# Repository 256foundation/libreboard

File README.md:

# Libre-Board
Open Source Bitcoin Mining Control Board.
Learn more at https://libreboard.org/

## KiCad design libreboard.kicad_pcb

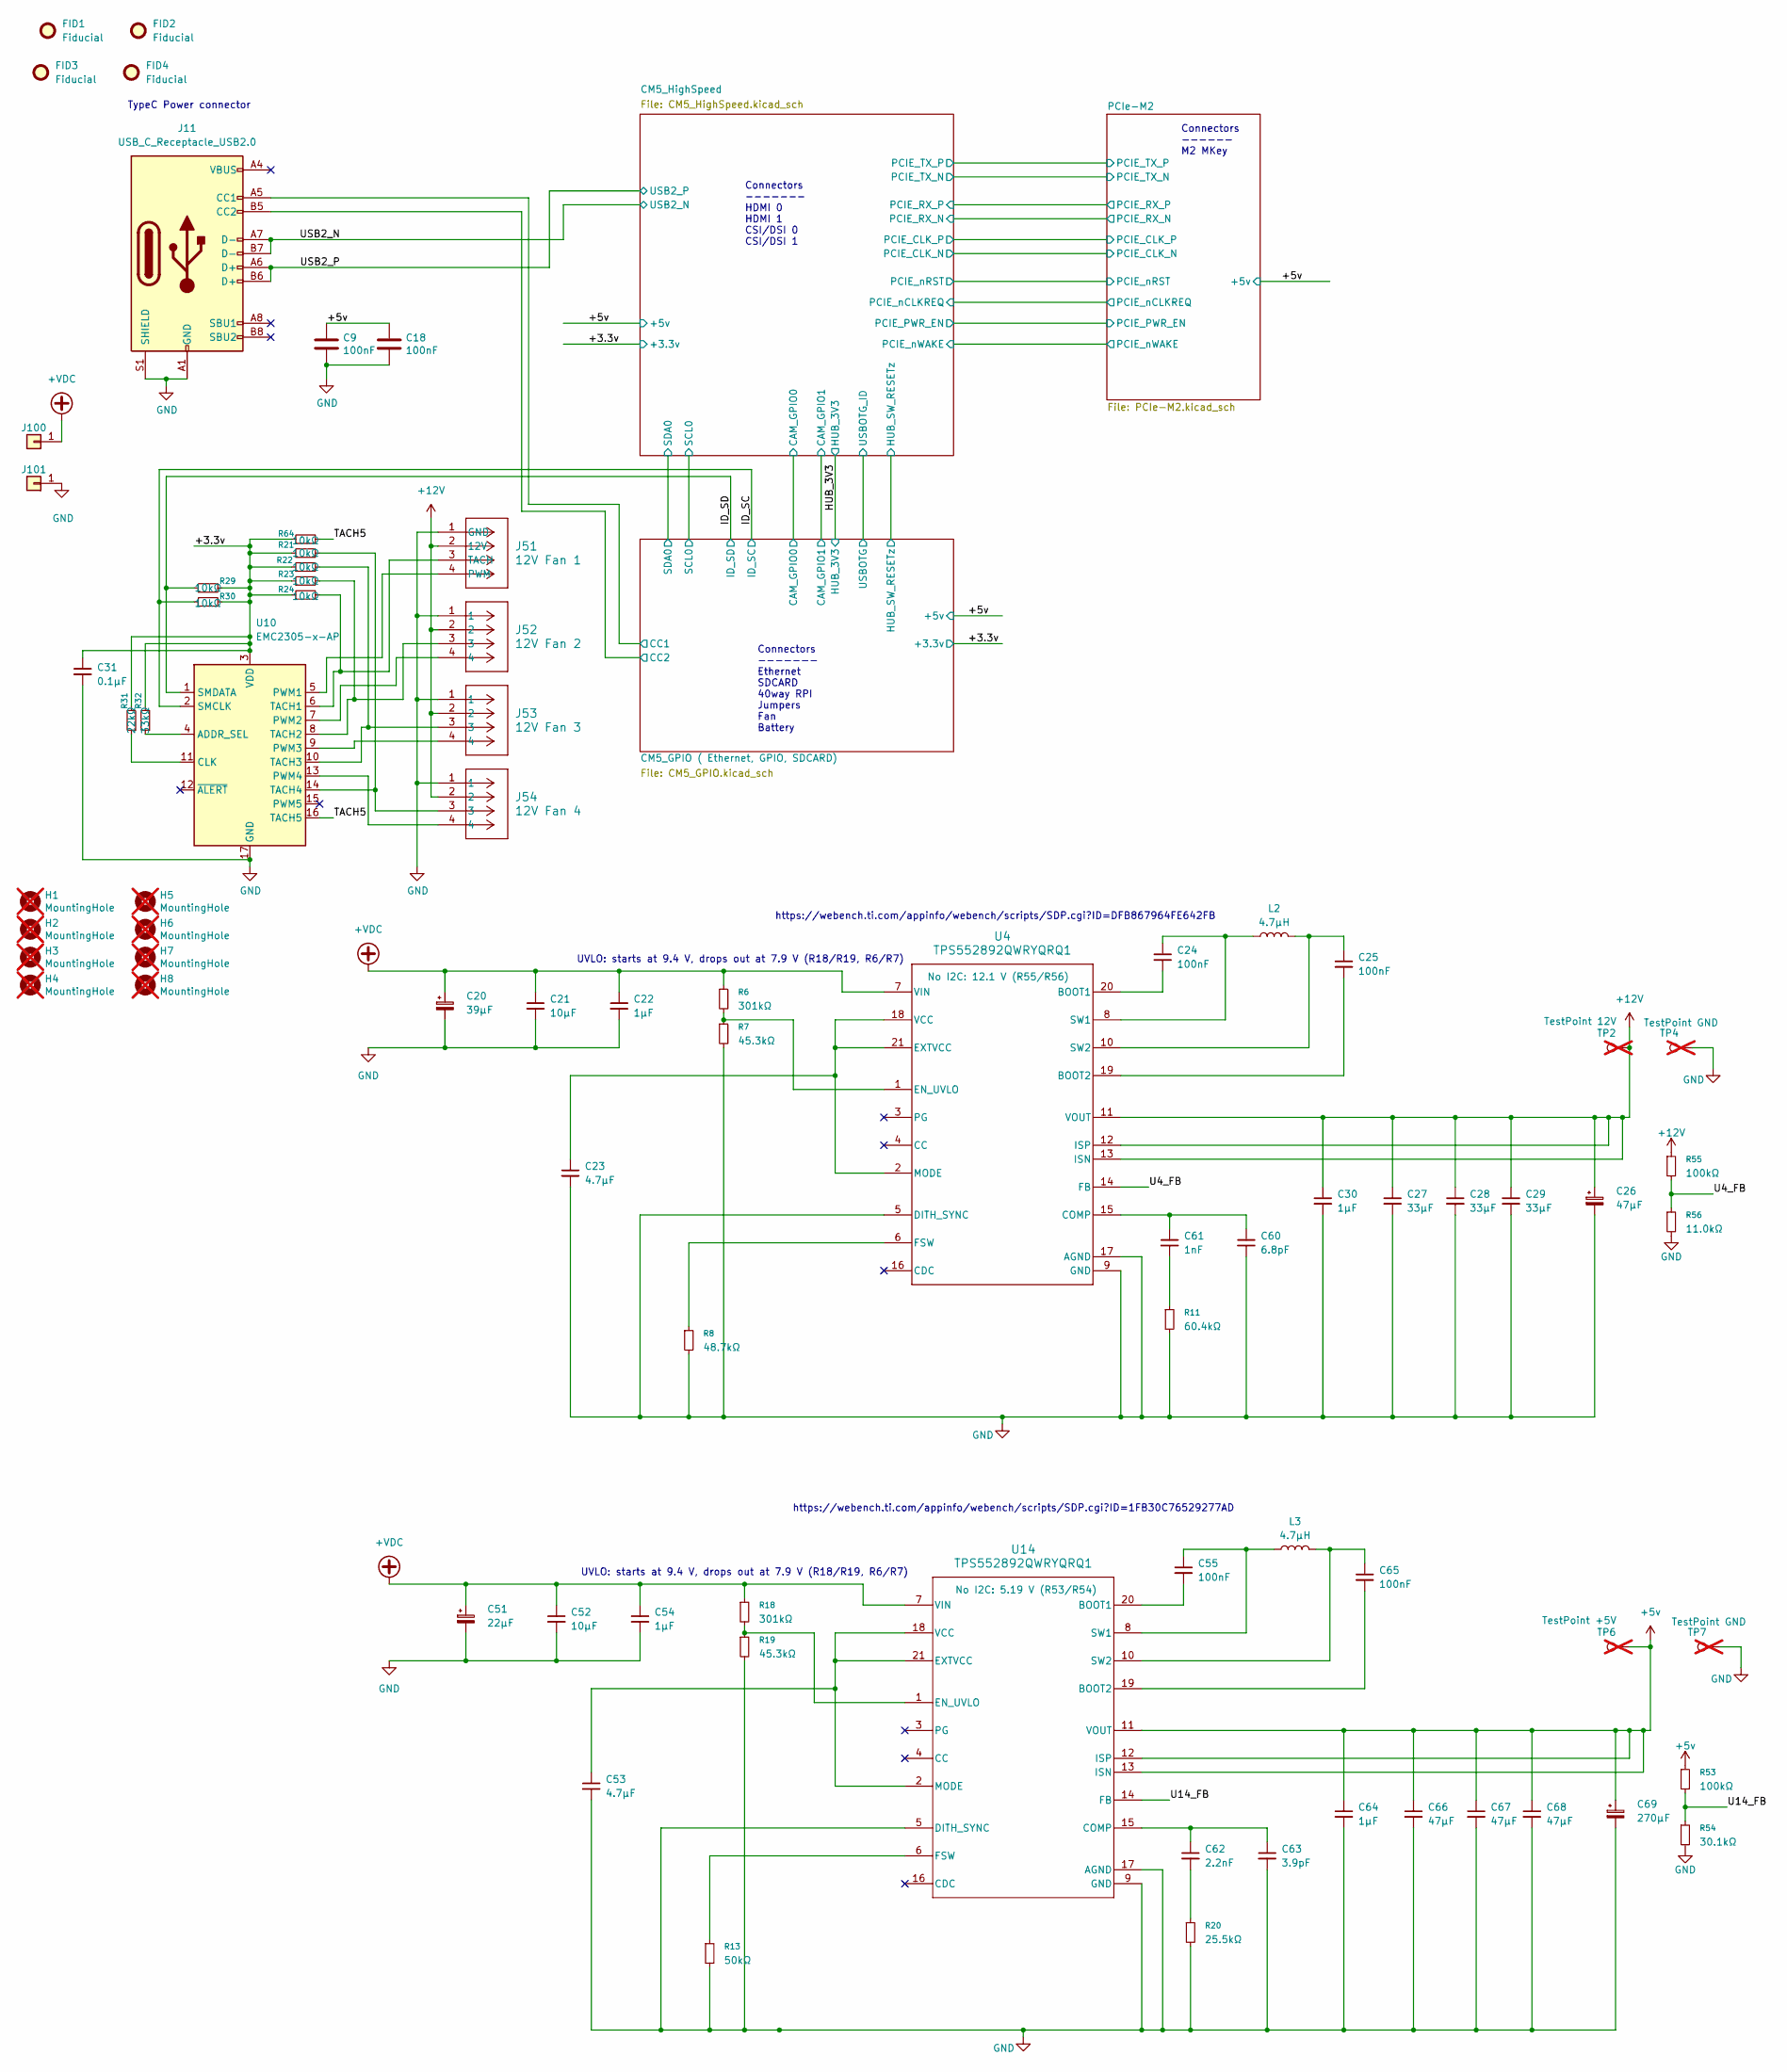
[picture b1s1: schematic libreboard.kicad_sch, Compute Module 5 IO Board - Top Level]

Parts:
C9, C18: 100nF; C_0402_1005Metric; Part Description Capacitor, Ceramic, 0.1µF, ±10%, 6.3V, 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; LCSC C1525
C20: 39µF; CP_Elec_8x6.7; Part Description Capacitor, Aluminum, 39µF, ±20%, 50V, 4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; LCSC C7059708
C21, C52: 10µF; C_0805_2012Metric; Part Description 10 µF ±10% 50V Ceramic Capacitor X5R 08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; LCSC C440198
C22, C30, C54: 1µF; C_0402_1005Metric; Part Description 1 µF ±10% 50V Ceramic Capacitor X5R 040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; LCSC C1518208
C23, C53: 4.7µF; C_1206_3216Metric; Part Description Capacitor, Ceramic, 4.7µF, ±10%, 50V, X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; LCSC C29823
C24, C25, C55, C65: 100nF; C_0402_1005Metric; Part Description CAP CER 0.1UF 50V X7R 0402; LCSC C307331
C26: 47µF; CP_Elec_5x5.9; Part Description Capacitor, Polymer Aluminum, 47µF, ±20%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; LCSC C54864098
C27, C28, C29: 33µF; C_1206_3216Metric; Part Description 33 µF ±20% 25V Ceramic Capacitor X5R 12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; LCSC C342307
C31: 0.1µF; C_0402_1005Metric; Part Description Capacitor, Ceramic, 0.1µF, ±10%, 6.3V, 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; LCSC C1525
C51: 22µF; CP_Elec_6.3x5.9; Part Description Capacitor, Aluminum, 22µF, ±20%, 50V, 4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; LCSC C46550474
C60: 6.8pF; C_0402_1005Metric; Part Description Capacitor, Ceramic, 6.8pF, ±0.25pF, 50V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; LCSC C1576
C61: 1nF; C_0402_1005Metric; Part Description Capacitor, Ceramic, 1nF, ±5%, 50V, C0G/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; LCSC C76947
C62: 2.2nF; C_0402_1005Metric; Part Description Capacitor, Ceramic, 2.2nF, ±10%, 50V, X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; LCSC C1531
C63: 3.9pF; C_0402_1005Metric; Part Description Capacitor, Ceramic, 3.9pF, ±2.5%, 50V, 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; LCSC C1517504
C64: 1µF; C_0402_1005Metric; Part Description Capacitor, Ceramic, 1µF, ±10%, 6.3V, X5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; LCSC C52923
C66, C67, C68: 47µF; C_1206_3216Metric; Part Description 47 µF ±20% 10V Ceramic Capacitor X5R 12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; LCSC C96123
C69: 270µF; CP_Elec_6.3x9.9; Part Description Capacitor, Aluminum, 270µF, ±20%, 10V, 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; LCSC C2944013
FID1, FID2, FID3, FID4: Fiducial; Fiducial_1mm_Mask2mm
H1, H2, H3, H4, H5, H6, H7, H8: MountingHole; MountingHole_2.7mm_M2.5_DIN965; Part Description M2.5 mounting hole; not fitted
J11: USB_C_Receptacle_USB2.0; USB_C_Receptacle_GCT_USB4105-xx-A_16P_TopMnt_Horizontal; Part Description Connector, USB-C, 2.0 data and power; LCSC C5184243
J51: 12V Fan 1; CONN_SD-47053-001_H10p00_MOL; Part Description Connector, Fan 1, 12V, 4 pin; LCSC C240840
J52: 12V Fan 2; CONN_SD-47053-001_H10p00_MOL; Part Description Connector, Fan 2, 12V, 4 pin; LCSC C240840
J53: 12V Fan 3; CONN_SD-47053-001_H10p00_MOL; Part Description Connector, Fan 3, 12V, 4 pin; LCSC C240840
J54: 12V Fan 4; CONN_SD-47053-001_H10p00_MOL; Part Description Connector, Fan 4, 12V, 4 pin; LCSC C240840
J100, J101: Screw Terminal; KEYSTONE_7790; PARTNO 36-7770; LCSC C5187194
L2, L3: 4.7µH; L_Bourns_SRN8040TA; Part Description FIXED IND 4.7UH 4.1A 24 MOHM SMD; LCSC C6685196
R6, R18: 301kΩ; R_0402_1005Metric; Part Description Resistor, 301kΩ, ±1%, 0.1W, SMD 0402 (1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; LCSC C7209900
R7, R19: 45.3kΩ; R_0402_1005Metric; Part Description Resistor, 45.3kΩ, ±1%, 0.1W, SMD 0402 (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; LCSC C2986582
R8: 48.7kΩ; R_0402_1005Metric; Part Description Resistor, 48.7kΩ, ±1%, 0.1W, SMD 0402 (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; LCSC C2077134
R11: 60.4kΩ; R_0402_1005Metric; Part Description Resistor, 60.4kΩ, ±1%, 0.1W, SMD 0402 (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; LCSC C2986234
R13: 50kΩ; R_0402_1005Metric; Part Description Resistor, 50kΩ, ±1%, 0.1W, SMD 0402 (10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; LCSC C7501196
R20: 25.5kΩ; R_0402_1005Metric; Part Description Resistor, 25.5kΩ, ±1%, 0.1W, SMD 0402 (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; LCSC C2076811
R21, R22, R23, R24, R29, R30, R64: 10kΩ; R_0402_1005Metric; Part Description Resistor, 10kΩ, ±1%, 0.1W, SMD 0402 (10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; LCSC C25744
R31: 22kΩ; R_0402_1005Metric; Part Description Resistor, 22kΩ, ±1%, 0.1W, SMD 0402 (10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; LCSC C25768
R32: 33kΩ; R_0402_1005Metric; Part Description Resistor, 33kΩ, ±1%, 0.1W, SMD 0402 (10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; LCSC C25779
R53, R55: 100kΩ; R_0402_1005Metric; Part Description Resistor, 100kΩ, ±1%, 0.1W, SMD 0402 (1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; LCSC C25741
R54: 30.1kΩ; R_0402_1005Metric; Part Description Resistor, 30.1kΩ, ±1%, 0.1W, SMD 0402 (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; LCSC C2076806
R56: 11.0kΩ; R_0402_1005Metric; Part Description Resistor, 11.0kΩ, ±1%, 0.1W, SMD 0402 (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; LCSC C409880
TP2: TestPoint 12V; TestPoint_Pad_D1.5mm; Part Description Test point; not fitted
TP4, TP7: TestPoint GND; TestPoint_Pad_D1.5mm; Part Description Test point; not fitted
TP6: TestPoint +5V; TestPoint_Pad_D1.5mm; Part Description Test point; not fitted
U4, U14: TPS552892QWRYQRQ1; RYQ0021A-MFG; Part Description IC, Buck Boost, 0.8-22V, 1-output, 8A, 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; LCSC C22375748
U10: EMC2305-x-AP; Texas_RGV0016A_VQFN-16-1EP_4x4mm_P0.65mm_EP2.1x2.1mm_Therma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; Part Description Motor Driver, PWM, 16-QFN, 4x4; LCSC C621415

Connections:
+5v: C9.1, C18.1, C64.1, C66.1, C67.1, C68.1, C69.1, R53.1, TP6.1 (1_1), U14.11 (VOUT), U14.12 (ISP), U14.13 (ISN); also elsewhere on the board
+12V: C26.1, C27.1, C28.1, C29.1, C30.1, J51.2 (12V), J52.2, J53.2, J54.2, R55.1, TP2.1 (1_1), U4.11 (VOUT), U4.12 (ISP), U4.13 (ISN)
+VDC: C20.1, C21.1, C22.1, C51.1, C52.1, C54.1, J100.1 (Pin_1_1), R6.1, R18.1, U4.7 (VIN), U14.7 (VIN)
/+3.3v: C31.1, R21.1, R22.1, R23.1, R24.1, R29.2, R30.2, R31.2, R32.2, R64.1, U10.3 (VDD); also elsewhere on the board
/CM5_GPIO ( Ethernet, GPIO, SDCARD)/CC1: J11.A5 (CC1); also elsewhere on the board
/CM5_GPIO ( Ethernet, GPIO, SDCARD)/CC2: J11.B5 (CC2); also elsewhere on the board
/ID_SC: R30.1, U10.2 (SMCLK); also elsewhere on the board
/ID_SD: R29.1, U10.1 (SMDATA); also elsewhere on the board
/TACH5: R64.2, U10.16 (TACH5)
/U4_FB: R55.2, R56.1, U4.14 (FB)
/U14_FB: R53.2, R54.1, U14.14 (FB)
/USB2_N: J11.A7 (D-), J11.B7 (D-); also elsewhere on the board
/USB2_P: J11.A6 (D+), J11.B6 (D+); also elsewhere on the board
GND: C9.2, C18.2, C20.2, C21.2, C22.2, C23.2, C26.2, C27.2, C28.2, C29.2, C30.2, C31.2, C51.2, C52.2, C53.2, C54.2, C60.2, C63.2, C64.2, C66.2, C67.2, C68.2, C69.2, J11.A1 (GND), J11.A12 (GND), J11.B1 (GND), J11.B12 (GND), J11.S1 (SHIELD), J51.1 (GND), J52.1, J53.1, J54.1, J101.1 (Pin_1_1), R7.2, R8.2, R11.2, R13.2, R19.2, R20.2, R54.2, R56.2, TP4.1 (1_1), TP7.1 (1_1), U4.5 (DITH_SYNC), U4.9 (GND), U4.17 (AGND), U10.17 (GND), U14.5 (DITH_SYNC), U14.9 (GND), U14.17 (AGND); also elsewhere on the board
unnamed: C61.2, R11.1
unnamed: C62.2, R20.1
unnamed: J51.4 (PWM), U10.5 (PWM1)
unnamed: J51.3 (TACH), R24.2, U10.6 (TACH1)
unnamed: C24.2, U4.20 (BOOT1)
unnamed: C25.2, U4.19 (BOOT2)
unnamed: C60.1, C61.1, U4.15 (COMP)
unnamed: R6.2, R7.1, U4.1 (EN_UVLO)
unnamed: C23.1, U4.2 (MODE), U4.18 (VCC), U4.21 (EXTVCC)
unnamed: R8.1, U4.6 (FSW)
unnamed: C24.1, L2.1, U4.8 (SW1)
unnamed: C25.1, L2.2, U4.10 (SW2)
unnamed: R32.1, U10.4 (ADDR_SEL)
unnamed: R31.1, U10.11 (CLK)
unnamed: J52.4, U10.7 (PWM2)
unnamed: J53.4, U10.9 (PWM3)
unnamed: J54.4, U10.13 (PWM4)
unnamed: J52.3, R23.2, U10.8 (TACH2)
unnamed: J53.3, R22.2, U10.10 (TACH3)
unnamed: J54.3, R21.2, U10.14 (TACH4)
unnamed: C55.2, U14.20 (BOOT1)
unnamed: C65.2, U14.19 (BOOT2)
unnamed: C62.1, C63.1, U14.15 (COMP)
unnamed: R18.2, R19.1, U14.1 (EN_UVLO)
unnamed: C53.1, U14.2 (MODE), U14.18 (VCC), U14.21 (EXTVCC)
unnamed: R13.1, U14.6 (FSW)
unnamed: C55.1, L3.1, U14.8 (SW1)
unnamed: C65.1, L3.2, U14.10 (SW2)

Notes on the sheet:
Connectors ------- Ethernet SDCARD 40way RPI Jumpers Fan Battery
Connectors ------ M2 MKey
UVLO: starts at 9.4 V, drops out at 7.9 V (R18/R19, R6/R7)
TypeC Power connector
Connectors ------- HDMI 0 HDMI 1 CSI/DSI 0 CSI/DSI 1
https://webench.ti.com/appinfo/webench/scripts/SDP.cgi?ID=1FB30C76529277AD
https://webench.ti.com/appinfo/webench/scripts/SDP.cgi?ID=DFB867964FE642FB

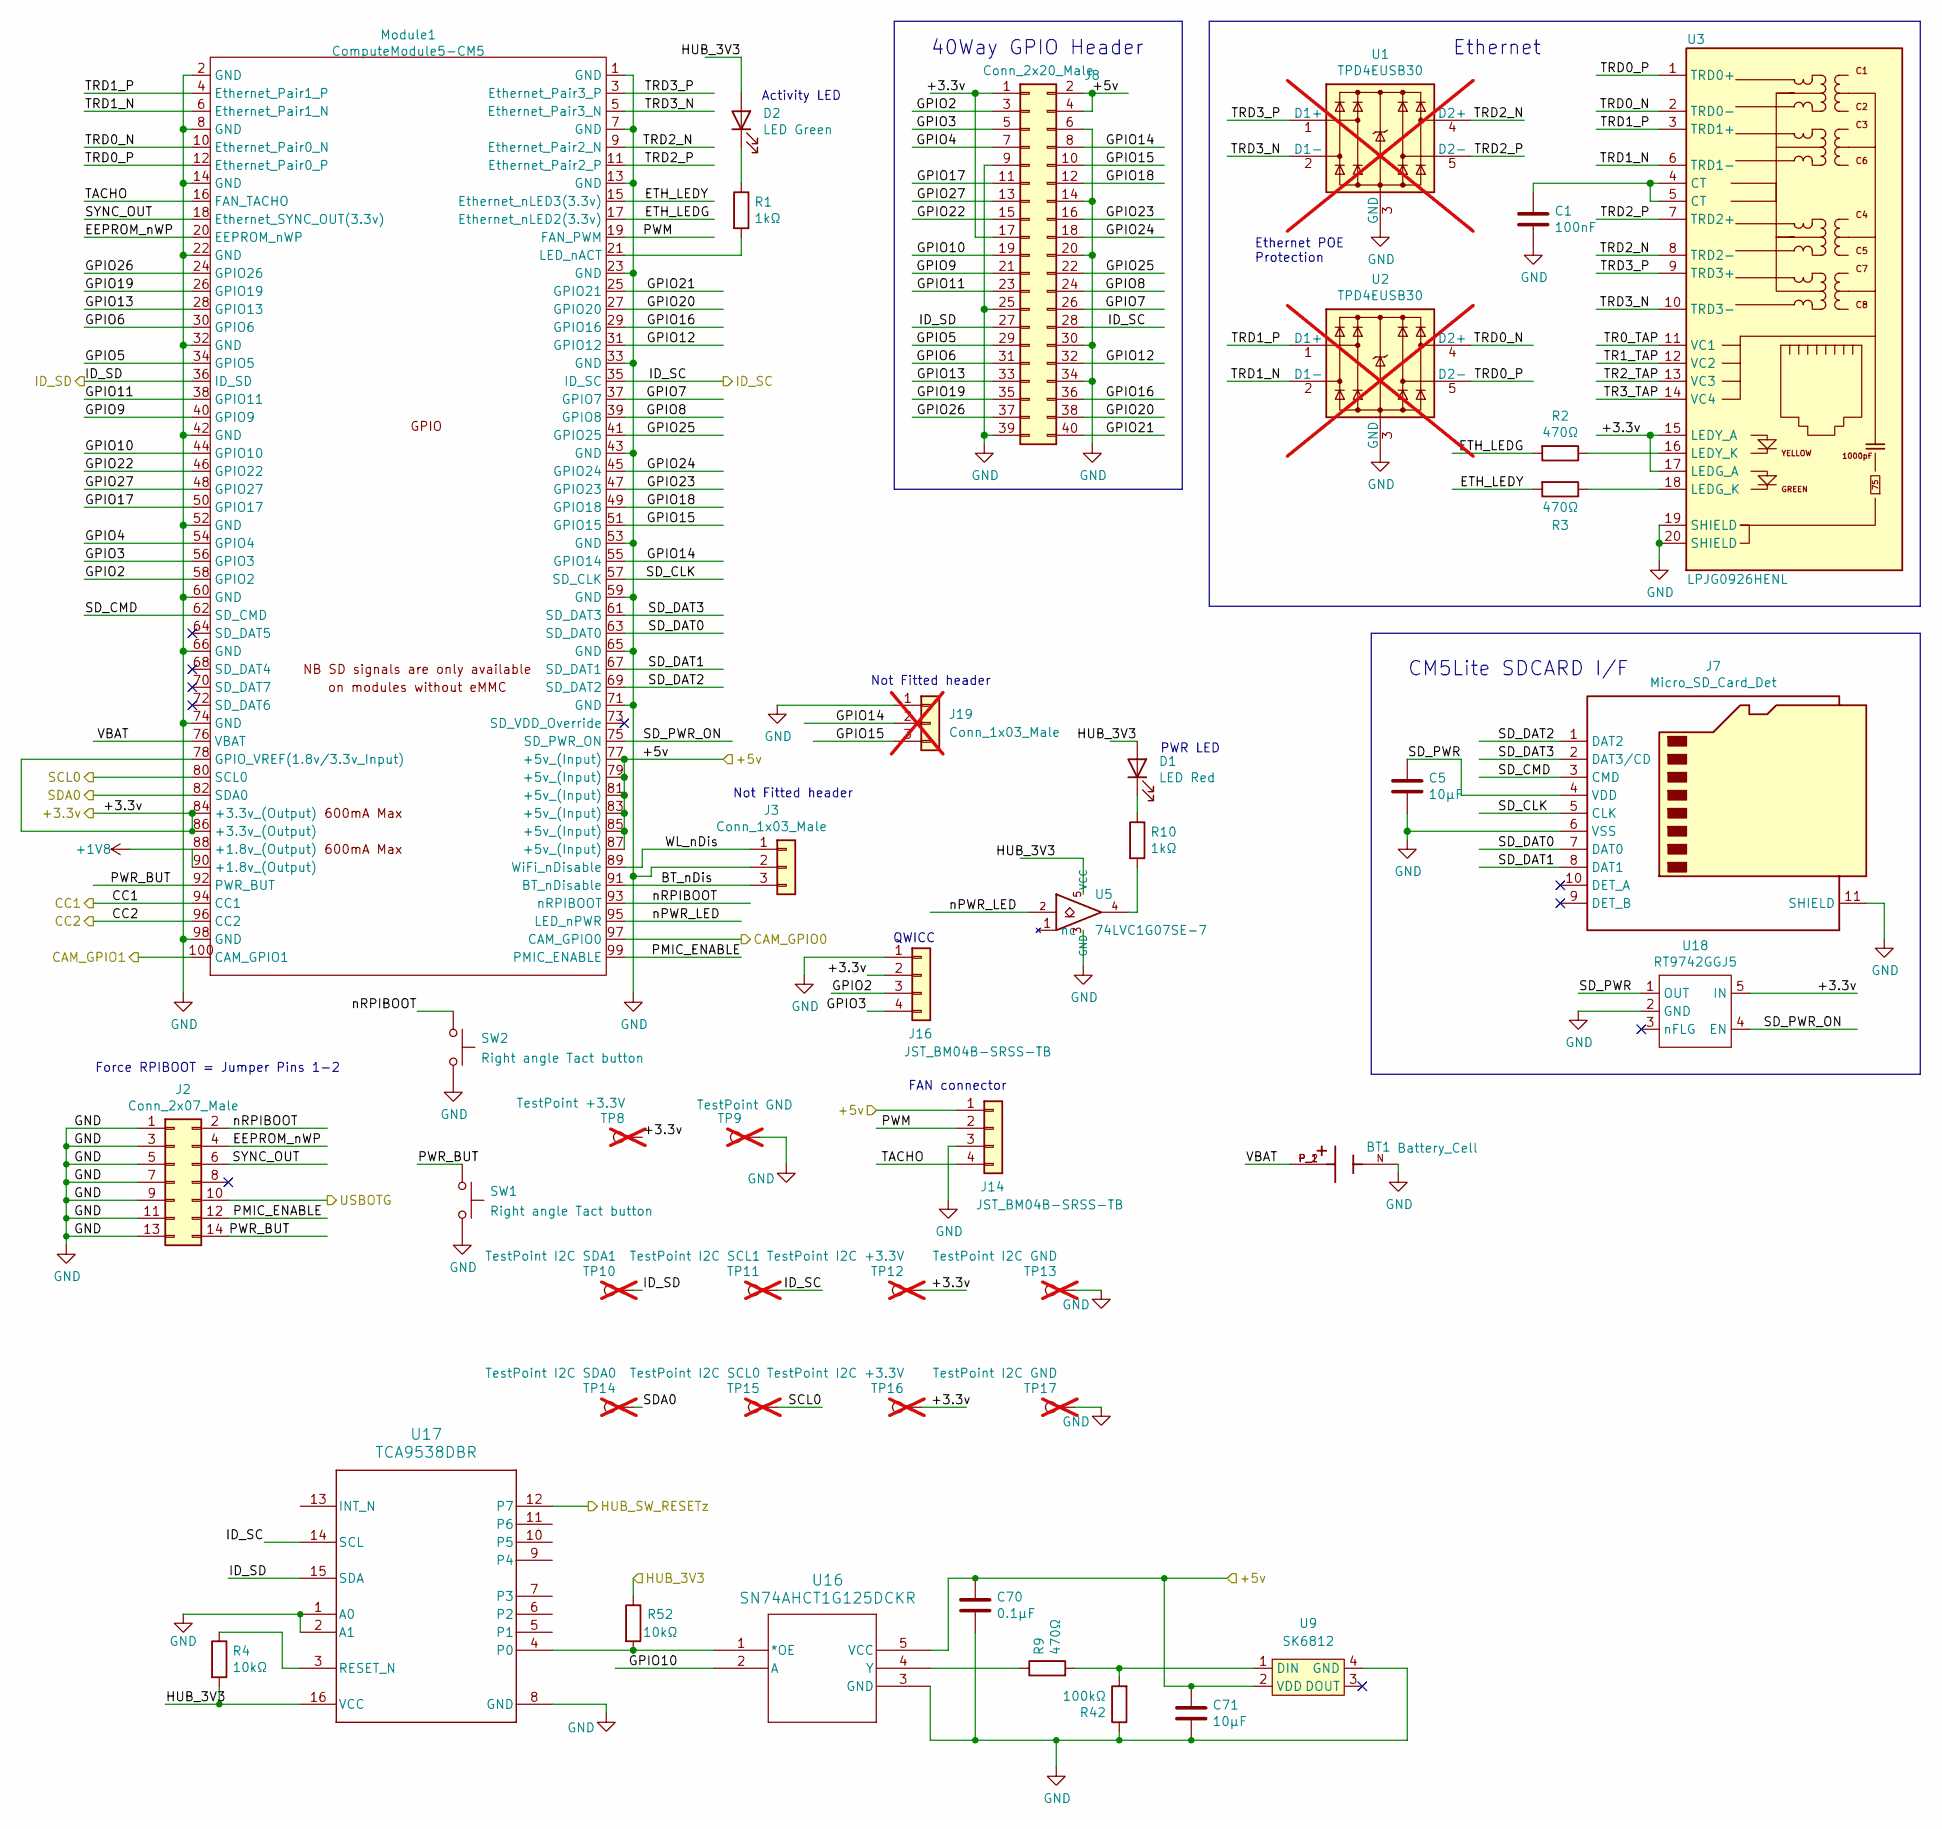
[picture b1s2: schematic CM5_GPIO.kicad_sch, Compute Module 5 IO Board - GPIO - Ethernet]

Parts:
BT1: Battery_Cell; BAT_BAT-HLD-007-SMT-TR; Part Description BATTERY RETAINER COIN 12MM SMD (CR1216/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; LCSC C6997853
C1: 100nF; C_0402_1005Metric; Part Description Capacitor, Ceramic, 0.1µF, ±10%, 6.3V, 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; LCSC C1525
C5: 10µF; C_0805_2012Metric; Part Description Capacitor, Ceramic, 10µF, ±10%, 10V, X5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; LCSC C15850
C70: 0.1µF; C_0402_1005Metric; Part Description Capacitor, Ceramic, 0.1µF, ±10%, 6.3V, 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; LCSC C1525
C71: 10µF; C_0402_1005Metric; Part Description Capacitor, Ceramic, 10µF, ±20%, 10V, X5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; LCSC C408132
D1: LED Red; LED_0603_1608Metric; Part Description LED, Red, 620nm, 2.2V, SMD 0603; LCSC C125114
D2: LED Green; LED_0603_1608Metric; Part Description LED, Green, 572nm, 2.2V, SMD 0603; LCSC C125113
J2: Conn_2x07_Male; PinHeader_2x07_P2.54mm_Vertical; Part Description Pin Header, Male, 2x07, 2.54mm P, Verti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; LCSC C71397
J3: Conn_1x03_Male; PinHeader_1x03_P2.54mm_Vertical; Part Description Pin Header, Male, 1x03, 2.54mm P, Verti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; LCSC C505002
J7: Micro_SD_Card_Det; SDCARD_MOLEX_503398-1892; Part Description 9 (8 + 1) Position Card Connector micro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; LCSC C428492
J8: Conn_2x20_Male; PinHeader_2x20_P2.54mm_Vertical; Part Description Pin Header, Male, 2x20, 2.54mm P, Verti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; LCSC C5364405
J14, J16: JST_BM04B-SRSS-TB; JST_SH_BM04B-SRSS-TB_1x04-1MP_P1.00mm_Vertical; Part Description Connector, Male, 1x04, vertical, 1mm P; LCSC C160390
J19: Conn_1x03_Male; PinHeader_1x03_P2.54mm_Vertical; Part Description Pin Header, Male, 1x03, 2.54mm P, Verti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; LCSC C505002; not fitted
Module1: ComputeModule5-CM5; CM5_Connector_A; Part Description Connector, CM Receptacle, 100 pin, 0.4m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
R1, R10: 1kΩ; R_0402_1005Metric; Part Description Resistor, 1kΩ, ±1%, 0.1W, SMD 0402 (100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; LCSC C11702
R2, R3, R9: 470Ω; R_0402_1005Metric; Part Description Resistor, 470Ω, ±1%, 0.1W, SMD 0402 (10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; LCSC C25117
R4, R52: 10kΩ; R_0402_1005Metric; Part Description Resistor, 10kΩ, ±1%, 0.1W, SMD 0402 (10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; LCSC C25744
R42: 100kΩ; R_0402_1005Metric; Part Description Resistor, 100kΩ, ±1%, 0.1W, SMD 0402 (1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; LCSC C25741
SW1, SW2: Right angle Tact button; SW_Tactile_SPST_Angled_PTS645Vx39-2LFS; Part Description Switch, Tactile, SPST-NO, Right Angle; LCSC C285519
TP8: TestPoint +3.3V; TestPoint_Pad_D1.5mm; Part Description Test point; not fitted
TP9: TestPoint GND; TestPoint_Pad_D1.5mm; Part Description Test point; not fitted
TP10: TestPoint I2C SDA1; TestPoint_Pad_D1.0mm; Part Description Test point; not fitted
TP11: TestPoint I2C SCL1; TestPoint_Pad_D1.0mm; Part Description Test point; not fitted
TP12, TP16: TestPoint I2C +3.3V; TestPoint_Pad_D1.5mm; Part Description Test point; not fitted
TP13, TP17: TestPoint I2C GND; TestPoint_Pad_D1.5mm; Part Description Test point; not fitted
TP14: TestPoint I2C SDA0; TestPoint_Pad_D1.5mm; Part Description Test point; not fitted
TP15: TestPoint I2C SCL0; TestPoint_Pad_D1.5mm; Part Description Test point; not fitted
U1, U2: TPD4EUSB30; USON-10_2.5x1.0mm_P0.5mm; Part Description Diode, TVS, 8V clamp, 1A; LCSC C90627; not fitted
U3: LPJG0926HENL; TRJG0926HENL; Part Description Receptacle, RJ45, 1Gb; LCSC C22457393
U5: 74LVC1G07SE-7; SOT-353_SC-70-5; Part Description Buffer, Non-Inverting, 1 Element, 1 Bit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; LCSC C67531
U9: SK6812; LED-SMD_4P-L4.0-W1.6-L; Part Description LED, RGB, 475-620nm, 3.7v-5.5v, SMD; LCSC C2890037
U16: SN74AHCT1G125DCKR; SOT-353_SC-70-5; Part Description Buffer, Non-Inverting 1 Element 1 Bit p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; LCSC C350557
U17: TCA9538DBR; DB0016A_N; Part Description I/O Expander 8 I2C 400 kHz 16-SSOP; LCSC C2652331
U18: RT9742GGJ5; SOT-23-5; Part Description Power Switch/Driver, 1:1, N-Channel, 1A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; LCSC C250547

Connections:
+1V8: Module1.88 (+1.8v_(Output)), Module1.90 (+1.8v_(Output)); also elsewhere on the board
+5v: C70.1, C71.1, J8.2, J8.4, J14.1, Module1.77 (+5v_(Input)), Module1.79 (+5v_(Input)), Module1.81 (+5v_(Input)), Module1.83 (+5v_(Input)), Module1.85 (+5v_(Input)), Module1.87 (+5v_(Input)), U9.2 (VDD), U16.5 (VCC); also elsewhere on the board
/+3.3v: J8.1, J8.17, J16.2, Module1.78 (GPIO_VREF(1.8v/3.3v_Input)), Module1.84 (+3.3v_(Output)), Module1.86 (+3.3v_(Output)), TP8.1 (1_1), TP12.1 (1_1), TP16.1 (1_1), U3.15 (LEDY_A), U3.17 (LEDG_A), U18.5 (IN); also elsewhere on the board
/CM5_GPIO ( Ethernet, GPIO, SDCARD)/BT_nDis: J3.3, Module1.91 (BT_nDisable)
/CM5_GPIO ( Ethernet, GPIO, SDCARD)/CAM_GPIO0: Module1.97 (CAM_GPIO0); also elsewhere on the board
/CM5_GPIO ( Ethernet, GPIO, SDCARD)/CAM_GPIO1: Module1.100 (CAM_GPIO1); also elsewhere on the board
/CM5_GPIO ( Ethernet, GPIO, SDCARD)/CC1: Module1.94 (CC1); also elsewhere on the board
/CM5_GPIO ( Ethernet, GPIO, SDCARD)/CC2: Module1.96 (CC2); also elsewhere on the board
/CM5_GPIO ( Ethernet, GPIO, SDCARD)/EEPROM_nWP: J2.4, Module1.20 (EEPROM_nWP)
/CM5_GPIO ( Ethernet, GPIO, SDCARD)/ETH_LEDG: Module1.17 (Ethernet_nLED2(3.3v)), R2.2
/CM5_GPIO ( Ethernet, GPIO, SDCARD)/ETH_LEDY: Module1.15 (Ethernet_nLED3(3.3v)), R3.2
/CM5_GPIO ( Ethernet, GPIO, SDCARD)/GPIO2: J8.3, J16.3, Module1.58 (GPIO2)
/CM5_GPIO ( Ethernet, GPIO, SDCARD)/GPIO3: J8.5, J16.4, Module1.56 (GPIO3)
/CM5_GPIO ( Ethernet, GPIO, SDCARD)/GPIO4: J8.7, Module1.54 (GPIO4)
/CM5_GPIO ( Ethernet, GPIO, SDCARD)/GPIO5: J8.29, Module1.34 (GPIO5)
/CM5_GPIO ( Ethernet, GPIO, SDCARD)/GPIO6: J8.31, Module1.30 (GPIO6)
/CM5_GPIO ( Ethernet, GPIO, SDCARD)/GPIO7: J8.26, Module1.37 (GPIO7)
/CM5_GPIO ( Ethernet, GPIO, SDCARD)/GPIO8: J8.24, Module1.39 (GPIO8)
/CM5_GPIO ( Ethernet, GPIO, SDCARD)/GPIO9: J8.21, Module1.40 (GPIO9)
/CM5_GPIO ( Ethernet, GPIO, SDCARD)/GPIO10: J8.19, Module1.44 (GPIO10), U16.2 (A)
/CM5_GPIO ( Ethernet, GPIO, SDCARD)/GPIO11: J8.23, Module1.38 (GPIO11)
/CM5_GPIO ( Ethernet, GPIO, SDCARD)/GPIO12: J8.32, Module1.31 (GPIO12)
/CM5_GPIO ( Ethernet, GPIO, SDCARD)/GPIO13: J8.33, Module1.28 (GPIO13)
/CM5_GPIO ( Ethernet, GPIO, SDCARD)/GPIO14: J8.8, J19.2, Module1.55 (GPIO14)
/CM5_GPIO ( Ethernet, GPIO, SDCARD)/GPIO15: J8.10, J19.3, Module1.51 (GPIO15)
/CM5_GPIO ( Ethernet, GPIO, SDCARD)/GPIO16: J8.36, Module1.29 (GPIO16)
/CM5_GPIO ( Ethernet, GPIO, SDCARD)/GPIO17: J8.11, Module1.50 (GPIO17)
/CM5_GPIO ( Ethernet, GPIO, SDCARD)/GPIO18: J8.12, Module1.49 (GPIO18)
/CM5_GPIO ( Ethernet, GPIO, SDCARD)/GPIO19: J8.35, Module1.26 (GPIO19)
/CM5_GPIO ( Ethernet, GPIO, SDCARD)/GPIO20: J8.38, Module1.27 (GPIO20)
/CM5_GPIO ( Ethernet, GPIO, SDCARD)/GPIO21: J8.40, Module1.25 (GPIO21)
/CM5_GPIO ( Ethernet, GPIO, SDCARD)/GPIO22: J8.15, Module1.46 (GPIO22)
/CM5_GPIO ( Ethernet, GPIO, SDCARD)/GPIO23: J8.16, Module1.47 (GPIO23)
/CM5_GPIO ( Ethernet, GPIO, SDCARD)/GPIO24: J8.18, Module1.45 (GPIO24)
/CM5_GPIO ( Ethernet, GPIO, SDCARD)/GPIO25: J8.22, Module1.41 (GPIO25)
/CM5_GPIO ( Ethernet, GPIO, SDCARD)/GPIO26: J8.37, Module1.24 (GPIO26)
/CM5_GPIO ( Ethernet, GPIO, SDCARD)/GPIO27: J8.13, Module1.48 (GPIO27)
/CM5_GPIO ( Ethernet, GPIO, SDCARD)/HUB_SW_RESETz: U17.12 (P7); also elsewhere on the board
/CM5_GPIO ( Ethernet, GPIO, SDCARD)/PMIC_ENABLE: J2.12, Module1.99 (PMIC_ENABLE)
/CM5_GPIO ( Ethernet, GPIO, SDCARD)/PWM: J14.2, Module1.19 (FAN_PWM)
/CM5_GPIO ( Ethernet, GPIO, SDCARD)/PWR_BUT: J2.14, Module1.92 (PWR_BUT), SW1.1
/CM5_GPIO ( Ethernet, GPIO, SDCARD)/SCL0: Module1.80 (SCL0), TP15.1 (1_1); also elsewhere on the board
/CM5_GPIO ( Ethernet, GPIO, SDCARD)/SDA0: Module1.82 (SDA0), TP14.1 (1_1); also elsewhere on the board
/CM5_GPIO ( Ethernet, GPIO, SDCARD)/SD_CLK: J7.5 (CLK), Module1.57 (SD_CLK)
/CM5_GPIO ( Ethernet, GPIO, SDCARD)/SD_CMD: J7.3 (CMD), Module1.62 (SD_CMD)
/CM5_GPIO ( Ethernet, GPIO, SDCARD)/SD_DAT0: J7.7 (DAT0), Module1.63 (SD_DAT0)
/CM5_GPIO ( Ethernet, GPIO, SDCARD)/SD_DAT1: J7.8 (DAT1), Module1.67 (SD_DAT1)
/CM5_GPIO ( Ethernet, GPIO, SDCARD)/SD_DAT2: J7.1 (DAT2), Module1.69 (SD_DAT2)
/CM5_GPIO ( Ethernet, GPIO, SDCARD)/SD_DAT3: J7.2 (DAT3/CD), Module1.61 (SD_DAT3)
/CM5_GPIO ( Ethernet, GPIO, SDCARD)/SD_PWR: C5.1, J7.4 (VDD), U18.1 (OUT)
/CM5_GPIO ( Ethernet, GPIO, SDCARD)/SD_PWR_ON: Module1.75 (SD_PWR_ON), U18.4 (EN)
/CM5_GPIO ( Ethernet, GPIO, SDCARD)/SYNC_OUT: J2.6, Module1.18 (Ethernet_SYNC_OUT(3.3v))
/CM5_GPIO ( Ethernet, GPIO, SDCARD)/TACHO: J14.4, Module1.16 (FAN_TACHO)
/CM5_GPIO ( Ethernet, GPIO, SDCARD)/TR0_TAP: U3.11 (VC1)
/CM5_GPIO ( Ethernet, GPIO, SDCARD)/TR1_TAP: U3.12 (VC2)
/CM5_GPIO ( Ethernet, GPIO, SDCARD)/TR2_TAP: U3.13 (VC3)
/CM5_GPIO ( Ethernet, GPIO, SDCARD)/TR3_TAP: U3.14 (VC4)
/CM5_GPIO ( Ethernet, GPIO, SDCARD)/TRD0_N: Module1.10 (Ethernet_Pair0_N), U2.4 (D2+), U2.7, U3.2 (TRD0-)
/CM5_GPIO ( Ethernet, GPIO, SDCARD)/TRD0_P: Module1.12 (Ethernet_Pair0_P), U2.5 (D2-), U2.6, U3.1 (TRD0+)
/CM5_GPIO ( Ethernet, GPIO, SDCARD)/TRD1_N: Module1.6 (Ethernet_Pair1_N), U2.2 (D1-), U2.9, U3.6 (TRD1-)
/CM5_GPIO ( Ethernet, GPIO, SDCARD)/TRD1_P: Module1.4 (Ethernet_Pair1_P), U2.1 (D1+), U2.10, U3.3 (TRD1+)
/CM5_GPIO ( Ethernet, GPIO, SDCARD)/TRD2_N: Module1.9 (Ethernet_Pair2_N), U1.4 (D2+), U1.7, U3.8 (TRD2-)
/CM5_GPIO ( Ethernet, GPIO, SDCARD)/TRD2_P: Module1.11 (Ethernet_Pair2_P), U1.5 (D2-), U1.6, U3.7 (TRD2+)
/CM5_GPIO ( Ethernet, GPIO, SDCARD)/TRD3_N: Module1.5 (Ethernet_Pair3_N), U1.2 (D1-), U1.9, U3.10 (TRD3-)
/CM5_GPIO ( Ethernet, GPIO, SDCARD)/TRD3_P: Module1.3 (Ethernet_Pair3_P), U1.1 (D1+), U1.10, U3.9 (TRD3+)
/CM5_GPIO ( Ethernet, GPIO, SDCARD)/USBOTG: J2.10; also elsewhere on the board
/CM5_GPIO ( Ethernet, GPIO, SDCARD)/VBAT: BT1.P_1, BT1.P_2, Module1.76 (VBAT)
/CM5_GPIO ( Ethernet, GPIO, SDCARD)/WL_nDis: J3.1, Module1.89 (WiFi_nDisable)
/CM5_GPIO ( Ethernet, GPIO, SDCARD)/nPWR_LED: Module1.95 (LED_nPWR), U5.2
/CM5_GPIO ( Ethernet, GPIO, SDCARD)/nRPIBOOT: J2.2, Module1.93 (nRPIBOOT), SW2.1
/HUB_3V3: D1.2 (A), D2.2 (A), R4.2, R52.1, U5.5 (VCC), U17.16 (VCC); also elsewhere on the board
/ID_SC: J8.28, Module1.35 (ID_SC), TP11.1 (1_1), U17.14 (SCL); also elsewhere on the board
/ID_SD: J8.27, Module1.36 (ID_SD), TP10.1 (1_1), U17.15 (SDA); also elsewhere on the board
GND: BT1.N, C1.2, C5.2, C70.2, C71.2, J2.1, J2.3, J2.5, J2.7, J2.9, J2.11, J2.13, J3.2, J7.6 (VSS), J7.11 (SHIELD), J8.6, J8.9, J8.14, J8.20, J8.25, J8.30, J8.34, J8.39, J14.3, J16.1, J19.1, Module1.1 (GND), Module1.2 (GND), Module1.7 (GND), Module1.8 (GND), Module1.13 (GND), Module1.14 (GND), Module1.22 (GND), Module1.23 (GND), Module1.32 (GND), Module1.33 (GND), Module1.42 (GND), Module1.43 (GND), Module1.52 (GND), Module1.53 (GND), Module1.59 (GND), Module1.60 (GND), Module1.65 (GND), Module1.66 (GND), Module1.71 (GND), Module1.74 (GND), Module1.98 (GND), R42.1, SW1.2, SW2.2, TP9.1 (1_1), TP13.1 (1_1), TP17.1 (1_1), U1.3 (GND), U1.8 (GND), U2.3 (GND), U2.8 (GND), U3.19 (SHIELD), U3.20 (SHIELD), U5.3 (GND), U9.4 (GND), U16.3 (GND), U17.1 (A0), U17.2 (A1), U17.8 (GND), U18.2 (GND); also elsewhere on the board
unnamed: C1.1, U3.4 (CT), U3.5 (CT)
unnamed: D1.1 (K), R10.1
unnamed: D2.1 (K), R1.1
unnamed: Module1.21 (LED_nACT), R1.2
unnamed: R10.2, U5.4
unnamed: R3.1, U3.18 (LEDG_K)
unnamed: R2.1, U3.16 (LEDY_K)
unnamed: R9.2, R42.2, U9.1 (DIN)
unnamed: R52.2, U16.1 (*OE), U17.4 (P0)
unnamed: R9.1, U16.4 (Y)
unnamed: R4.1, U17.3 (RESET_N)

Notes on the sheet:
QWICC
40Way GPIO Header
Activity LED
FAN connector
Ethernet POE Protection
Not Fitted header
Force RPIBOOT = Jumper Pins 1-2
PWR LED
Ethernet
CM5Lite SDCARD I/F

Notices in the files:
CM5_GPIO.kicad_sch:
Copyright © 2024 Raspberry Pi Ltd.
